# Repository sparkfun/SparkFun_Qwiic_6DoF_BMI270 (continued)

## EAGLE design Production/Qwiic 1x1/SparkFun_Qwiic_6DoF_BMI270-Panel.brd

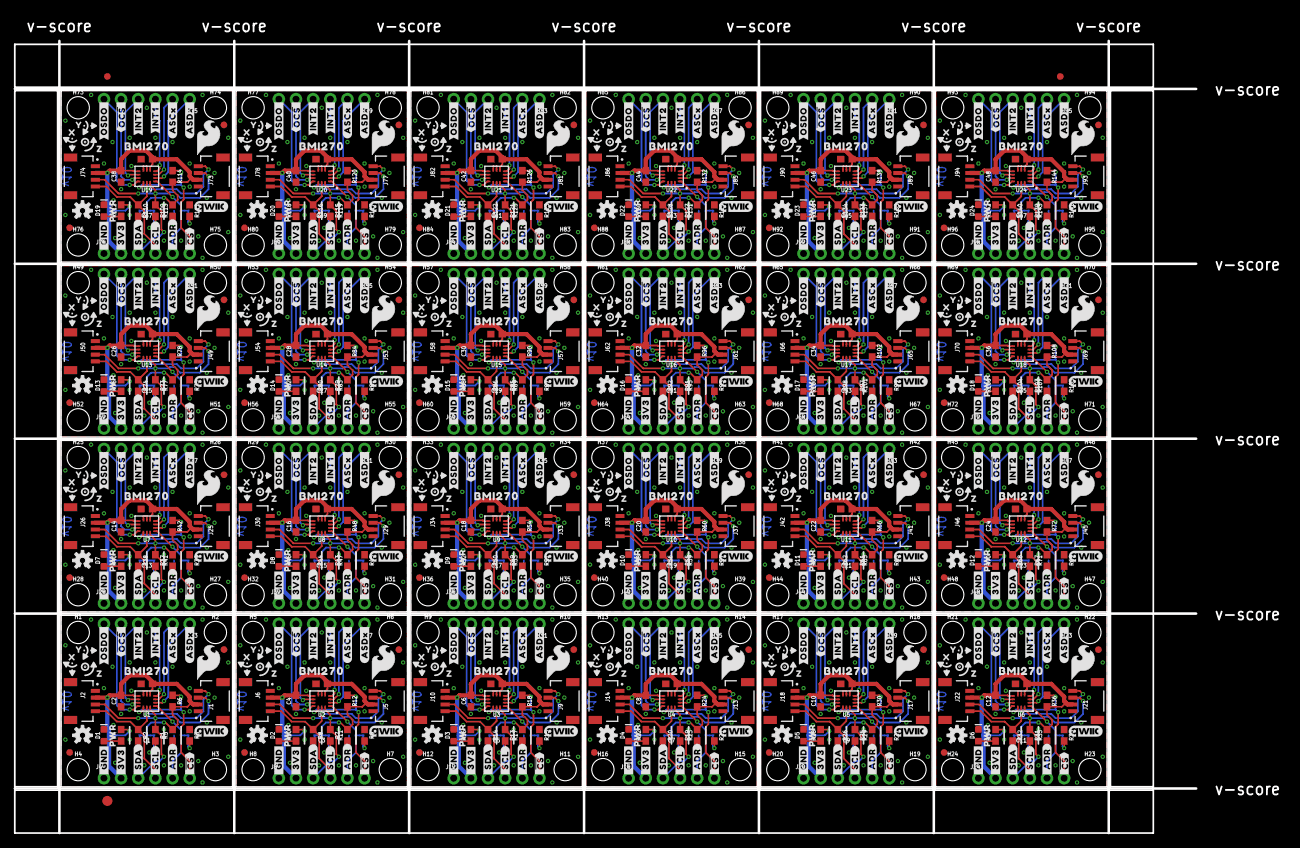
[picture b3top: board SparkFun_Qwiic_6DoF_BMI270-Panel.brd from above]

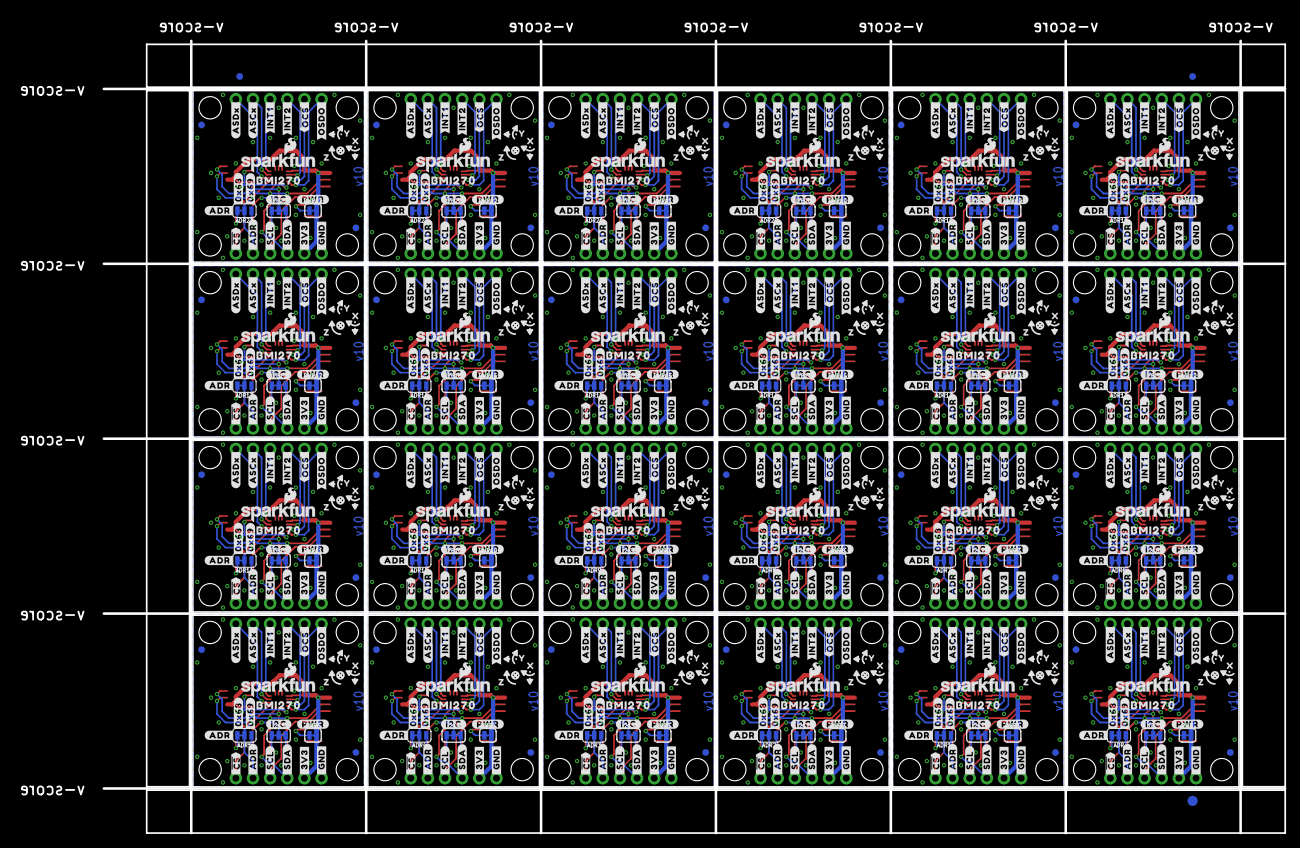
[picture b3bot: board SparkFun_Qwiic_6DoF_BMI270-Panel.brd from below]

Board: 2 copper layers, 175.0 x 117.3 mm, 1614 parts (651 on the bottom side), 432 nets.

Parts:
ADR, ADR1, ADR2, ADR3, ADR4, ADR5, ADR6, ADR7, ADR8, ADR9, ADR10, ADR11, ADR12, ADR13, ADR14, ADR15, ADR16, ADR17, ADR18, ADR19, ADR20, ADR21, ADR22, ADR23: JUMPER-SMT_3_1-NC_TRACE_SILK; SMT-JUMPER_3_1-NC_TRACE_SILK
C1, C2, C3, C4, C5, C6, C7, C8, C9, C10, C11, C12, C13, C14, C15, C16, C17, C18, C19, C20, C21, C22, C23, C24, C25, C26, C27, C28, C29, C30, C31, C32, C33, C34, C35, C36, C37, C38, C39, C40, C41, C42, C43, C44, C45, C46, C47, C48: 0.1uF; 0603
D1, D2, D3, D4, D5, D6, D7, D8, D9, D10, D11, D12, D13, D14, D15, D16, D17, D18, D19, D20, D21, D22, D23, D24: RED; LED-0603
E$1, E$2, E$3, E$4: FIDUCIAL-1X2
E$5, E$6: FIDUCIAL-1.5X3
FD1, FD2, FD3, FD4, FD5, FD6, FD7, FD8, FD9, FD10, FD11, FD12, FD13, FD14, FD15, FD16, FD17, FD18, FD19, FD20, FD21, FD22, FD23, FD24, FD25, FD26, FD27, FD28, FD29, FD30, FD31, FD32, FD33, FD34, FD35, FD36, FD37, FD38, FD39, FD40, FD41, FD42, FD43, FD44, FD45, FD46, FD47, FD48, FD49, FD50, FD51, FD52, FD53, FD54, FD55, FD56, FD57, FD58, FD59, FD60, FD61, FD62, FD63, FD64, FD65, FD66, FD67, FD68, FD69, FD70, FD71, FD72, FD73, FD74, FD75, FD76, FD77, FD78, FD79, FD80, FD81, FD82, FD83, FD84, FD85, FD86, FD87, FD88, FD89, FD90, FD91, FD92, FD93, FD94, FD95, FD96: FIDUCIAL1X2; FIDUCIAL-1X2
H1, H2, H3, H4, H5, H6, H7, H8, H9, H10, H11, H12, H13, H14, H15, H16, H17, H18, H19, H20, H21, H22, H23, H24, H25, H26, H27, H28, H29, H30, H31, H32, H33, H34, H35, H36, H37, H38, H39, H40, H41, H42, H43, H44, H45, H46, H47, H48, H49, H50, H51, H52, H53, H54, H55, H56, H57, H58, H59, H60, H61, H62, H63, H64, H65, H66, H67, H68, H69, H70, H71, H72, H73, H74, H75, H76, H77, H78, H79, H80, H81, H82, H83, H84, H85, H86, H87, H88, H89, H90, H91, H92, H93, H94, H95, H96: STAND-OFF
I2C, I2C1, I2C2, I2C3, I2C4, I2C5, I2C6, I2C7, I2C8, I2C9, I2C10, I2C11, I2C12, I2C13, I2C14, I2C15, I2C16, I2C17, I2C18, I2C19, I2C20, I2C21, I2C22, I2C23: JUMPER-SMT_3_2-NC_TRACE_SILK; SMT-JUMPER_3_2-NC_TRACE_SILK
J1, J2, J5, J6, J9, J10, J13, J14, J17, J18, J21, J22, J25, J26, J29, J30, J33, J34, J37, J38, J41, J42, J45, J46, J49, J50, J53, J54, J57, J58, J61, J62, J65, J66, J69, J70, J73, J74, J77, J78, J81, J82, J85, J86, J89, J90, J93, J94: QWIIC_RIGHT_ANGLE; JST04_1MM_RA
J3, J4, J7, J8, J11, J12, J15, J16, J19, J20, J23, J24, J27, J28, J31, J32, J35, J36, J39, J40, J43, J44, J47, J48, J51, J52, J55, J56, J59, J60, J63, J64, J67, J68, J71, J72, J75, J76, J79, J80, J83, J84, J87, J88, J91, J92, J95, J96: 1X06_NO_SILK
LOGO1, LOGO4, LOGO7, LOGO10, LOGO13, LOGO16, LOGO19, LOGO22, LOGO25, LOGO28, LOGO31, LOGO34, LOGO37, LOGO40, LOGO43, LOGO46, LOGO49, LOGO52, LOGO55, LOGO58, LOGO61, LOGO64, LOGO67, LOGO70: SFE_LOGO_NAME_FLAME.1_INCH; SFE_LOGO_NAME_FLAME_.1
LOGO2, LOGO5, LOGO8, LOGO11, LOGO14, LOGO17, LOGO20, LOGO23, LOGO26, LOGO29, LOGO32, LOGO35, LOGO38, LOGO41, LOGO44, LOGO47, LOGO50, LOGO53, LOGO56, LOGO59, LOGO62, LOGO65, LOGO68, LOGO71: QWIIC_LOGO_5MM; QWIIC_5MM
LOGO3, LOGO6, LOGO9, LOGO12, LOGO15, LOGO18, LOGO21, LOGO24, LOGO27, LOGO30, LOGO33, LOGO36, LOGO39, LOGO42, LOGO45, LOGO48, LOGO51, LOGO54, LOGO57, LOGO60, LOGO63, LOGO66, LOGO69, LOGO72: OSHW-LOGOS; OSHW-LOGO-S
PWR, PWR1, PWR2, PWR3, PWR4, PWR5, PWR6, PWR7, PWR8, PWR9, PWR10, PWR11, PWR12, PWR13, PWR14, PWR15, PWR16, PWR17, PWR18, PWR19, PWR20, PWR21, PWR22, PWR23: JUMPER-SMT_2_NC_TRACE_SILK; SMT-JUMPER_2_NC_TRACE_SILK
R1, R2, R7, R8, R13, R14, R19, R20, R25, R26, R31, R32, R37, R38, R43, R44, R49, R50, R55, R56, R61, R62, R67, R68, R73, R74, R79, R80, R85, R86, R91, R92, R97, R98, R103, R104, R109, R110, R115, R116, R121, R122, R127, R128, R133, R134, R139, R140: 2.2k; 0603
R3, R5, R6, R9, R11, R12, R15, R17, R18, R21, R23, R24, R27, R29, R30, R33, R35, R36, R39, R41, R42, R45, R47, R48, R51, R53, R54, R57, R59, R60, R63, R65, R66, R69, R71, R72, R75, R77, R78, R81, R83, R84, R87, R89, R90, R93, R95, R96, R99, R101, R102, R105, R107, R108, R111, R113, R114, R117, R119, R120, R123, R125, R126, R129, R131, R132, R135, R137, R138, R141, R143, R144: 100k; 0603
R4, R10, R16, R22, R28, R34, R40, R46, R52, R58, R64, R70, R76, R82, R88, R94, R100, R106, R112, R118, R124, R130, R136, R142: 4.7k; 0603
U1, U2, U3, U4, U5, U6, U7, U8, U9, U10, U11, U12, U13, U14, U15, U16, U17, U18, U19, U20, U21, U22, U23, U24: BMI270
U$1, U$38, U$77, U$122, U$161, U$200, U$239, U$278, U$317, U$356, U$395, U$434, U$473, U$512, U$551, U$590, U$629, U$668, U$707, U$746, U$785, U$824, U$863, U$902: #I2C#0
U$2, U$14, U$47, U$59, U$92, U$104, U$131, U$143, U$170, U$182, U$209, U$221, U$248, U$260, U$287, U$299, U$326, U$338, U$365, U$377, U$404, U$416, U$443, U$455, U$482, U$494, U$521, U$533, U$560, U$572, U$599, U$611, U$638, U$650, U$677, U$689, U$716, U$728, U$755, U$767, U$794, U$806, U$833, U$845, U$872, U$884, U$911, U$923: #_SDA#0
U$3, U$37, U$76, U$121, U$160, U$199, U$238, U$277, U$316, U$355, U$394, U$433, U$472, U$511, U$550, U$589, U$628, U$667, U$706, U$745, U$784, U$823, U$862, U$901: SFE_LOGO_FLAME_.2
U$4, U$39, U$78, U$123, U$162, U$201, U$240, U$279, U$318, U$357, U$396, U$435, U$474, U$513, U$552, U$591, U$630, U$669, U$708, U$747, U$786, U$825, U$864, U$903: #PWR#0
U$5, U$40, U$82, U$124, U$163, U$202, U$241, U$280, U$319, U$358, U$397, U$436, U$475, U$514, U$553, U$592, U$631, U$670, U$709, U$748, U$787, U$826, U$865, U$904: #ADR#0
U$6, U$41, U$83, U$125, U$164, U$203, U$242, U$281, U$320, U$359, U$398, U$437, U$476, U$515, U$554, U$593, U$632, U$671, U$710, U$749, U$788, U$827, U$866, U$905: #0X68#0
U$7, U$13, U$46, U$58, U$91, U$103, U$130, U$142, U$169, U$181, U$208, U$220, U$247, U$259, U$286, U$298, U$325, U$337, U$364, U$376, U$403, U$415, U$442, U$454, U$481, U$493, U$520, U$532, U$559, U$571, U$598, U$610, U$637, U$649, U$676, U$688, U$715, U$727, U$754, U$766, U$793, U$805, U$832, U$844, U$871, U$883, U$910, U$922: #_3V3#0
U$8, U$17, U$50, U$62, U$95, U$107, U$134, U$146, U$173, U$185, U$212, U$224, U$251, U$263, U$290, U$302, U$329, U$341, U$368, U$380, U$407, U$419, U$446, U$458, U$485, U$497, U$524, U$536, U$563, U$575, U$602, U$614, U$641, U$653, U$680, U$692, U$719, U$731, U$758, U$770, U$797, U$809, U$836, U$848, U$875, U$887, U$914, U$926: #_#CS##0
U$9, U$16, U$49, U$61, U$94, U$106, U$133, U$145, U$172, U$184, U$211, U$223, U$250, U$262, U$289, U$301, U$328, U$340, U$367, U$379, U$406, U$418, U$445, U$457, U$484, U$496, U$523, U$535, U$562, U$574, U$601, U$613, U$640, U$652, U$679, U$691, U$718, U$730, U$757, U$769, U$796, U$808, U$835, U$847, U$874, U$886, U$913, U$925: #_ADR#0
U$10, U$15, U$48, U$60, U$93, U$105, U$132, U$144, U$171, U$183, U$210, U$222, U$249, U$261, U$288, U$300, U$327, U$339, U$366, U$378, U$405, U$417, U$444, U$456, U$483, U$495, U$522, U$534, U$561, U$573, U$600, U$612, U$639, U$651, U$678, U$690, U$717, U$729, U$756, U$768, U$795, U$807, U$834, U$846, U$873, U$885, U$912, U$924: #_SCL#0
U$11, U$27, U$51, U$63, U$96, U$108, U$135, U$147, U$174, U$186, U$213, U$225, U$252, U$264, U$291, U$303, U$330, U$342, U$369, U$381, U$408, U$420, U$447, U$459, U$486, U$498, U$525, U$537, U$564, U$576, U$603, U$615, U$642, U$654, U$681, U$693, U$720, U$732, U$759, U$771, U$798, U$810, U$837, U$849, U$876, U$888, U$915, U$927: #ASDX_#0
U$12, U$19, U$45, U$57, U$87, U$102, U$129, U$141, U$168, U$180, U$207, U$219, U$246, U$258, U$285, U$297, U$324, U$336, U$363, U$375, U$402, U$414, U$441, U$453, U$480, U$492, U$519, U$531, U$558, U$570, U$597, U$609, U$636, U$648, U$675, U$687, U$714, U$726, U$753, U$765, U$792, U$804, U$831, U$843, U$870, U$882, U$909, U$921: #_GND#0
U$18, U$42, U$84, U$126, U$165, U$204, U$243, U$282, U$321, U$360, U$399, U$438, U$477, U$516, U$555, U$594, U$633, U$672, U$711, U$750, U$789, U$828, U$867, U$906: #0X69#0
U$20, U$21, U$43, U$44, U$85, U$86, U$127, U$128, U$166, U$167, U$205, U$206, U$244, U$245, U$283, U$284, U$322, U$323, U$361, U$362, U$400, U$401, U$439, U$440, U$478, U$479, U$517, U$518, U$556, U$557, U$595, U$596, U$634, U$635, U$673, U$674, U$712, U$713, U$751, U$752, U$790, U$791, U$829, U$830, U$868, U$869, U$907, U$908: BMI2700
U$22, U$28, U$52, U$64, U$97, U$109, U$136, U$148, U$175, U$187, U$214, U$226, U$253, U$265, U$292, U$304, U$331, U$343, U$370, U$382, U$409, U$421, U$448, U$460, U$487, U$499, U$526, U$538, U$565, U$577, U$604, U$616, U$643, U$655, U$682, U$694, U$721, U$733, U$760, U$772, U$799, U$811, U$838, U$850, U$877, U$889, U$916, U$928: #ASCX_#0
U$23, U$29, U$53, U$65, U$98, U$110, U$137, U$149, U$176, U$188, U$215, U$227, U$254, U$266, U$293, U$305, U$332, U$344, U$371, U$383, U$410, U$422, U$449, U$461, U$488, U$500, U$527, U$539, U$566, U$578, U$605, U$617, U$644, U$656, U$683, U$695, U$722, U$734, U$761, U$773, U$800, U$812, U$839, U$851, U$878, U$890, U$917, U$929: #INT1_#0
U$24, U$30, U$54, U$66, U$99, U$111, U$138, U$150, U$177, U$189, U$216, U$228, U$255, U$267, U$294, U$306, U$333, U$345, U$372, U$384, U$411, U$423, U$450, U$462, U$489, U$501, U$528, U$540, U$567, U$579, U$606, U$618, U$645, U$657, U$684, U$696, U$723, U$735, U$762, U$774, U$801, U$813, U$840, U$852, U$879, U$891, U$918, U$930: #INT2_#0
U$25, U$31, U$55, U$67, U$100, U$112, U$139, U$151, U$178, U$190, U$217, U$229, U$256, U$268, U$295, U$307, U$334, U$346, U$373, U$385, U$412, U$424, U$451, U$463, U$490, U$502, U$529, U$541, U$568, U$580, U$607, U$619, U$646, U$658, U$685, U$697, U$724, U$736, U$763, U$775, U$802, U$814, U$841, U$853, U$880, U$892, U$919, U$931: ##OCS#_#0
U$26, U$32, U$56, U$68, U$101, U$113, U$140, U$152, U$179, U$191, U$218, U$230, U$257, U$269, U$296, U$308, U$335, U$347, U$374, U$386, U$413, U$425, U$452, U$464, U$491, U$503, U$530, U$542, U$569, U$581, U$608, U$620, U$647, U$659, U$686, U$698, U$725, U$737, U$764, U$776, U$803, U$815, U$842, U$854, U$881, U$893, U$920, U$932: #OSDO_#0
U$33, U$69, U$73, U$79, U$88, U$114, U$118, U$153, U$157, U$192, U$196, U$231, U$235, U$270, U$274, U$309, U$313, U$348, U$352, U$387, U$391, U$426, U$430, U$465, U$469, U$504, U$508, U$543, U$547, U$582, U$586, U$621, U$625, U$660, U$664, U$699, U$703, U$738, U$742, U$777, U$781, U$816, U$820, U$855, U$859, U$894, U$898, U$933: X0
U$34, U$72, U$117, U$156, U$195, U$234, U$273, U$312, U$351, U$390, U$429, U$468, U$507, U$546, U$585, U$624, U$663, U$702, U$741, U$780, U$819, U$858, U$897, U$936: PWR0
U$35, U$70, U$74, U$80, U$89, U$115, U$119, U$154, U$158, U$193, U$197, U$232, U$236, U$271, U$275, U$310, U$314, U$349, U$353, U$388, U$392, U$427, U$431, U$466, U$470, U$505, U$509, U$544, U$548, U$583, U$587, U$622, U$626, U$661, U$665, U$700, U$704, U$739, U$743, U$778, U$782, U$817, U$821, U$856, U$860, U$895, U$899, U$934: Y0
U$36, U$71, U$75, U$81, U$90, U$116, U$120, U$155, U$159, U$194, U$198, U$233, U$237, U$272, U$276, U$311, U$315, U$350, U$354, U$389, U$393, U$428, U$432, U$467, U$471, U$506, U$510, U$545, U$549, U$584, U$588, U$623, U$627, U$662, U$666, U$701, U$705, U$740, U$744, U$779, U$783, U$818, U$822, U$857, U$861, U$896, U$900, U$935: Z0

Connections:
3.3V: C1.2, C2.2, I2C.2, J1.2, J2.2, J4.2, PWR.2, R5.2, R6.2, U1.5, U1.8
3.3V1: C3.2, C4.2, I2C1.2, J5.2, J6.2, J8.2, PWR1.2, R11.2, R12.2, U2.5, U2.8
3.3V2: C5.2, C6.2, I2C2.2, J9.2, J10.2, J12.2, PWR2.2, R17.2, R18.2, U3.5, U3.8
3.3V3: C7.2, C8.2, I2C3.2, J13.2, J14.2, J16.2, PWR3.2, R23.2, R24.2, U4.5, U4.8
3.3V4: C9.2, C10.2, I2C4.2, J17.2, J18.2, J20.2, PWR4.2, R29.2, R30.2, U5.5, U5.8
3.3V5: C11.2, C12.2, I2C5.2, J21.2, J22.2, J24.2, PWR5.2, R35.2, R36.2, U6.5, U6.8
3.3V6: C13.2, C14.2, I2C6.2, J25.2, J26.2, J28.2, PWR6.2, R41.2, R42.2, U7.5, U7.8
3.3V7: C15.2, C16.2, I2C7.2, J29.2, J30.2, J32.2, PWR7.2, R47.2, R48.2, U8.5, U8.8
3.3V8: C17.2, C18.2, I2C8.2, J33.2, J34.2, J36.2, PWR8.2, R53.2, R54.2, U9.5, U9.8
3.3V9: C19.2, C20.2, I2C9.2, J37.2, J38.2, J40.2, PWR9.2, R59.2, R60.2, U10.5, U10.8
3.3V10: C21.2, C22.2, I2C10.2, J41.2, J42.2, J44.2, PWR10.2, R65.2, R66.2, U11.5, U11.8
3.3V11: C23.2, C24.2, I2C11.2, J45.2, J46.2, J48.2, PWR11.2, R71.2, R72.2, U12.5, U12.8
3.3V12: C25.2, C26.2, I2C12.2, J49.2, J50.2, J52.2, PWR12.2, R77.2, R78.2, U13.5, U13.8
3.3V13: C27.2, C28.2, I2C13.2, J53.2, J54.2, J56.2, PWR13.2, R83.2, R84.2, U14.5, U14.8
3.3V14: C29.2, C30.2, I2C14.2, J57.2, J58.2, J60.2, PWR14.2, R89.2, R90.2, U15.5, U15.8
3.3V15: C31.2, C32.2, I2C15.2, J61.2, J62.2, J64.2, PWR15.2, R95.2, R96.2, U16.5, U16.8
3.3V16: C33.2, C34.2, I2C16.2, J65.2, J66.2, J68.2, PWR16.2, R101.2, R102.2, U17.5, U17.8
3.3V17: C35.2, C36.2, I2C17.2, J69.2, J70.2, J72.2, PWR17.2, R107.2, R108.2, U18.5, U18.8
3.3V18: C37.2, C38.2, I2C18.2, J73.2, J74.2, J76.2, PWR18.2, R113.2, R114.2, U19.5, U19.8
3.3V19: C39.2, C40.2, I2C19.2, J77.2, J78.2, J80.2, PWR19.2, R119.2, R120.2, U20.5, U20.8
3.3V20: C41.2, C42.2, I2C20.2, J81.2, J82.2, J84.2, PWR20.2, R125.2, R126.2, U21.5, U21.8
3.3V21: C43.2, C44.2, I2C21.2, J85.2, J86.2, J88.2, PWR21.2, R131.2, R132.2, U22.5, U22.8
3.3V22: C45.2, C46.2, I2C22.2, J89.2, J90.2, J92.2, PWR22.2, R137.2, R138.2, U23.5, U23.8
3.3V23: C47.2, C48.2, I2C23.2, J93.2, J94.2, J96.2, PWR23.2, R143.2, R144.2, U24.5, U24.8
!CS!: J4.6, R6.1, U1.12
!CS!1: J8.6, R12.1, U2.12
!CS!2: J12.6, R18.1, U3.12
!CS!3: J16.6, R24.1, U4.12
!CS!4: J20.6, R30.1, U5.12
!CS!5: J24.6, R36.1, U6.12
!CS!6: J28.6, R42.1, U7.12
!CS!7: J32.6, R48.1, U8.12
!CS!8: J36.6, R54.1, U9.12
!CS!9: J40.6, R60.1, U10.12
!CS!10: J44.6, R66.1, U11.12
!CS!11: J48.6, R72.1, U12.12
!CS!12: J52.6, R78.1, U13.12
!CS!13: J56.6, R84.1, U14.12
!CS!14: J60.6, R90.1, U15.12
!CS!15: J64.6, R96.1, U16.12
!CS!16: J68.6, R102.1, U17.12
!CS!17: J72.6, R108.1, U18.12
!CS!18: J76.6, R114.1, U19.12
!CS!19: J80.6, R120.1, U20.12
!CS!20: J84.6, R126.1, U21.12
!CS!21: J88.6, R132.1, U22.12
!CS!22: J92.6, R138.1, U23.12
!CS!23: J96.6, R144.1, U24.12
!OCS!: J3.5, U1.10
!OCS!1: J7.5, U2.10
!OCS!2: J11.5, U3.10
!OCS!3: J15.5, U4.10
!OCS!4: J19.5, U5.10
!OCS!5: J23.5, U6.10
!OCS!6: J27.5, U7.10
!OCS!7: J31.5, U8.10
!OCS!8: J35.5, U9.10
!OCS!9: J39.5, U10.10
!OCS!10: J43.5, U11.10
!OCS!11: J47.5, U12.10
!OCS!12: J51.5, U13.10
!OCS!13: J55.5, U14.10
!OCS!14: J59.5, U15.10
!OCS!15: J63.5, U16.10
!OCS!16: J67.5, U17.10
!OCS!17: J71.5, U18.10
!OCS!18: J75.5, U19.10
!OCS!19: J79.5, U20.10
!OCS!20: J83.5, U21.10
!OCS!21: J87.5, U22.10
!OCS!22: J91.5, U23.10
!OCS!23: J95.5, U24.10
ADR/POCI: ADR.2, J4.5, U1.1
ADR/POCI1: ADR1.2, J8.5, U2.1
ADR/POCI2: ADR2.2, J12.5, U3.1
ADR/POCI3: ADR3.2, J16.5, U4.1
ADR/POCI4: ADR4.2, J20.5, U5.1
ADR/POCI5: ADR5.2, J24.5, U6.1
ADR/POCI6: ADR6.2, J28.5, U7.1
ADR/POCI7: ADR7.2, J32.5, U8.1
ADR/POCI8: ADR8.2, J36.5, U9.1
ADR/POCI9: ADR9.2, J40.5, U10.1
ADR/POCI10: ADR10.2, J44.5, U11.1
ADR/POCI11: ADR11.2, J48.5, U12.1
ADR/POCI12: ADR12.2, J52.5, U13.1
ADR/POCI13: ADR13.2, J56.5, U14.1
ADR/POCI14: ADR14.2, J60.5, U15.1
ADR/POCI15: ADR15.2, J64.5, U16.1
ADR/POCI16: ADR16.2, J68.5, U17.1
ADR/POCI17: ADR17.2, J72.5, U18.1
ADR/POCI18: ADR18.2, J76.5, U19.1
ADR/POCI19: ADR19.2, J80.5, U20.1
ADR/POCI20: ADR20.2, J84.5, U21.1
ADR/POCI21: ADR21.2, J88.5, U22.1
ADR/POCI22: ADR22.2, J92.5, U23.1
ADR/POCI23: ADR23.2, J96.5, U24.1
ASCX: J3.2, U1.3
ASCX1: J7.2, U2.3
ASCX2: J11.2, U3.3
ASCX3: J15.2, U4.3
ASCX4: J19.2, U5.3
ASCX5: J23.2, U6.3
ASCX6: J27.2, U7.3
ASCX7: J31.2, U8.3
ASCX8: J35.2, U9.3
ASCX9: J39.2, U10.3
ASCX10: J43.2, U11.3
ASCX11: J47.2, U12.3
ASCX12: J51.2, U13.3
ASCX13: J55.2, U14.3
ASCX14: J59.2, U15.3
ASCX15: J63.2, U16.3
ASCX16: J67.2, U17.3
ASCX17: J71.2, U18.3
ASCX18: J75.2, U19.3
ASCX19: J79.2, U20.3
ASCX20: J83.2, U21.3
ASCX21: J87.2, U22.3
ASCX22: J91.2, U23.3
ASCX23: J95.2, U24.3
ASDX: J3.1, U1.2
ASDX1: J7.1, U2.2
ASDX2: J11.1, U3.2
ASDX3: J15.1, U4.2
ASDX4: J19.1, U5.2
ASDX5: J23.1, U6.2
ASDX6: J27.1, U7.2
ASDX7: J31.1, U8.2
ASDX8: J35.1, U9.2
ASDX9: J39.1, U10.2
ASDX10: J43.1, U11.2
ASDX11: J47.1, U12.2
ASDX12: J51.1, U13.2
ASDX13: J55.1, U14.2
ASDX14: J59.1, U15.2
ASDX15: J63.1, U16.2
ASDX16: J67.1, U17.2
ASDX17: J71.1, U18.2
ASDX18: J75.1, U19.2
ASDX19: J79.1, U20.2
ASDX20: J83.1, U21.2
ASDX21: J87.1, U22.2
ASDX22: J91.1, U23.2
ASDX23: J95.1, U24.2
GND: C1.1, C2.1, D1.C, J1.1, J2.1, J4.1, R3.1, U1.6, U1.7
GND1: C3.1, C4.1, D2.C, J5.1, J6.1, J8.1, R9.1, U2.6, U2.7
GND2: C5.1, C6.1, D3.C, J9.1, J10.1, J12.1, R15.1, U3.6, U3.7
GND3: C7.1, C8.1, D4.C, J13.1, J14.1, J16.1, R21.1, U4.6, U4.7
GND4: C9.1, C10.1, D5.C, J17.1, J18.1, J20.1, R27.1, U5.6, U5.7
GND5: C11.1, C12.1, D6.C, J21.1, J22.1, J24.1, R33.1, U6.6, U6.7
GND6: C13.1, C14.1, D7.C, J25.1, J26.1, J28.1, R39.1, U7.6, U7.7
GND7: C15.1, C16.1, D8.C, J29.1, J30.1, J32.1, R45.1, U8.6, U8.7
GND8: C17.1, C18.1, D9.C, J33.1, J34.1, J36.1, R51.1, U9.6, U9.7
GND9: C19.1, C20.1, D10.C, J37.1, J38.1, J40.1, R57.1, U10.6, U10.7
GND10: C21.1, C22.1, D11.C, J41.1, J42.1, J44.1, R63.1, U11.6, U11.7
GND11: C23.1, C24.1, D12.C, J45.1, J46.1, J48.1, R69.1, U12.6, U12.7
GND12: C25.1, C26.1, D13.C, J49.1, J50.1, J52.1, R75.1, U13.6, U13.7
GND13: C27.1, C28.1, D14.C, J53.1, J54.1, J56.1, R81.1, U14.6, U14.7
GND14: C29.1, C30.1, D15.C, J57.1, J58.1, J60.1, R87.1, U15.6, U15.7
GND15: C31.1, C32.1, D16.C, J61.1, J62.1, J64.1, R93.1, U16.6, U16.7
GND16: C33.1, C34.1, D17.C, J65.1, J66.1, J68.1, R99.1, U17.6, U17.7
GND17: C35.1, C36.1, D18.C, J69.1, J70.1, J72.1, R105.1, U18.6, U18.7
GND18: C37.1, C38.1, D19.C, J73.1, J74.1, J76.1, R111.1, U19.6, U19.7
GND19: C39.1, C40.1, D20.C, J77.1, J78.1, J80.1, R117.1, U20.6, U20.7
GND20: C41.1, C42.1, D21.C, J81.1, J82.1, J84.1, R123.1, U21.6, U21.7
GND21: C43.1, C44.1, D22.C, J85.1, J86.1, J88.1, R129.1, U22.6, U22.7
GND22: C45.1, C46.1, D23.C, J89.1, J90.1, J92.1, R135.1, U23.6, U23.7
GND23: C47.1, C48.1, D24.C, J93.1, J94.1, J96.1, R141.1, U24.6, U24.7
INT1: J3.3, U1.4
INT2: J3.4, U1.9
INT3: J7.3, U2.4
INT4: J7.4, U2.9
INT5: J11.3, U3.4
INT6: J11.4, U3.9
INT7: J15.3, U4.4
INT8: J15.4, U4.9
INT9: J19.3, U5.4
INT10: J19.4, U5.9
INT11: J23.3, U6.4
INT12: J23.4, U6.9
INT13: J27.3, U7.4
INT14: J27.4, U7.9
INT15: J31.3, U8.4
INT16: J31.4, U8.9
INT17: J35.3, U9.4
INT18: J35.4, U9.9
INT19: J39.3, U10.4
INT20: J39.4, U10.9
INT21: J43.3, U11.4
INT22: J43.4, U11.9
INT23: J47.3, U12.4
INT24: J47.4, U12.9
INT25: J51.3, U13.4
INT26: J51.4, U13.9
INT27: J55.3, U14.4
INT28: J55.4, U14.9
INT29: J59.3, U15.4
INT30: J59.4, U15.9
INT31: J63.3, U16.4
INT32: J63.4, U16.9
INT33: J67.3, U17.4
INT34: J67.4, U17.9
INT35: J71.3, U18.4
INT36: J71.4, U18.9
INT37: J75.3, U19.4
INT38: J75.4, U19.9
INT39: J79.3, U20.4
INT40: J79.4, U20.9
INT41: J83.3, U21.4
INT42: J83.4, U21.9
INT43: J87.3, U22.4
INT44: J87.4, U22.9
INT45: J91.3, U23.4
INT46: J91.4, U23.9
INT47: J95.3, U24.4
INT48: J95.4, U24.9
unnamed: I2C.1, R1.2
unnamed: I2C.3, R2.2
unnamed: PWR.1, R4.2
unnamed: D1.A, R4.1
unnamed: ADR.1, R5.1
unnamed: ADR.3, R3.2
unnamed: I2C1.1, R7.2
unnamed: I2C1.3, R8.2
unnamed: PWR1.1, R10.2
unnamed: D2.A, R10.1
unnamed: ADR1.1, R11.1
unnamed: ADR1.3, R9.2
unnamed: I2C2.1, R13.2
unnamed: I2C2.3, R14.2
unnamed: PWR2.1, R16.2
unnamed: D3.A, R16.1
unnamed: ADR2.1, R17.1
unnamed: ADR2.3, R15.2
unnamed: I2C3.1, R19.2
unnamed: I2C3.3, R20.2
unnamed: PWR3.1, R22.2
unnamed: D4.A, R22.1
unnamed: ADR3.1, R23.1
unnamed: ADR3.3, R21.2
unnamed: I2C4.1, R25.2
unnamed: I2C4.3, R26.2
unnamed: PWR4.1, R28.2
unnamed: D5.A, R28.1
unnamed: ADR4.1, R29.1
unnamed: ADR4.3, R27.2
unnamed: I2C5.1, R31.2
unnamed: I2C5.3, R32.2
unnamed: PWR5.1, R34.2
unnamed: D6.A, R34.1
unnamed: ADR5.1, R35.1
unnamed: ADR5.3, R33.2
unnamed: I2C6.1, R37.2
unnamed: I2C6.3, R38.2
unnamed: PWR6.1, R40.2
unnamed: D7.A, R40.1
unnamed: ADR6.1, R41.1
unnamed: ADR6.3, R39.2
unnamed: I2C7.1, R43.2
unnamed: I2C7.3, R44.2
unnamed: PWR7.1, R46.2
unnamed: D8.A, R46.1
unnamed: ADR7.1, R47.1
unnamed: ADR7.3, R45.2
unnamed: I2C8.1, R49.2
unnamed: I2C8.3, R50.2
unnamed: PWR8.1, R52.2
unnamed: D9.A, R52.1
unnamed: ADR8.1, R53.1
unnamed: ADR8.3, R51.2
unnamed: I2C9.1, R55.2
unnamed: I2C9.3, R56.2
unnamed: PWR9.1, R58.2
unnamed: D10.A, R58.1
unnamed: ADR9.1, R59.1
unnamed: ADR9.3, R57.2
unnamed: I2C10.1, R61.2
unnamed: I2C10.3, R62.2
unnamed: PWR10.1, R64.2
unnamed: D11.A, R64.1
unnamed: ADR10.1, R65.1
unnamed: ADR10.3, R63.2
unnamed: I2C11.1, R67.2
unnamed: I2C11.3, R68.2
unnamed: PWR11.1, R70.2
unnamed: D12.A, R70.1
unnamed: ADR11.1, R71.1
unnamed: ADR11.3, R69.2
unnamed: I2C12.1, R73.2
unnamed: I2C12.3, R74.2
unnamed: PWR12.1, R76.2
unnamed: D13.A, R76.1
unnamed: ADR12.1, R77.1
unnamed: ADR12.3, R75.2
unnamed: I2C13.1, R79.2
unnamed: I2C13.3, R80.2
unnamed: PWR13.1, R82.2
unnamed: D14.A, R82.1
unnamed: ADR13.1, R83.1
unnamed: ADR13.3, R81.2
unnamed: I2C14.1, R85.2
unnamed: I2C14.3, R86.2
unnamed: PWR14.1, R88.2
unnamed: D15.A, R88.1
unnamed: ADR14.1, R89.1
unnamed: ADR14.3, R87.2
unnamed: I2C15.1, R91.2
unnamed: I2C15.3, R92.2
unnamed: PWR15.1, R94.2
unnamed: D16.A, R94.1
unnamed: ADR15.1, R95.1
unnamed: ADR15.3, R93.2
unnamed: I2C16.1, R97.2
unnamed: I2C16.3, R98.2
unnamed: PWR16.1, R100.2
unnamed: D17.A, R100.1
unnamed: ADR16.1, R101.1
unnamed: ADR16.3, R99.2
unnamed: I2C17.1, R103.2
unnamed: I2C17.3, R104.2
unnamed: PWR17.1, R106.2
unnamed: D18.A, R106.1
unnamed: ADR17.1, R107.1
unnamed: ADR17.3, R105.2
unnamed: I2C18.1, R109.2
unnamed: I2C18.3, R110.2
unnamed: PWR18.1, R112.2
unnamed: D19.A, R112.1
unnamed: ADR18.1, R113.1
unnamed: ADR18.3, R111.2
unnamed: I2C19.1, R115.2
unnamed: I2C19.3, R116.2
unnamed: PWR19.1, R118.2
unnamed: D20.A, R118.1
unnamed: ADR19.1, R119.1
unnamed: ADR19.3, R117.2
unnamed: I2C20.1, R121.2
unnamed: I2C20.3, R122.2
unnamed: PWR20.1, R124.2
unnamed: D21.A, R124.1
unnamed: ADR20.1, R125.1
unnamed: ADR20.3, R123.2
unnamed: I2C21.1, R127.2
unnamed: I2C21.3, R128.2
unnamed: PWR21.1, R130.2
unnamed: D22.A, R130.1
unnamed: ADR21.1, R131.1
unnamed: ADR21.3, R129.2
unnamed: I2C22.1, R133.2
unnamed: I2C22.3, R134.2
unnamed: PWR22.1, R136.2
unnamed: D23.A, R136.1
unnamed: ADR22.1, R137.1
unnamed: ADR22.3, R135.2
unnamed: I2C23.1, R139.2
unnamed: I2C23.3, R140.2
unnamed: PWR23.1, R142.2
unnamed: D24.A, R142.1
unnamed: ADR23.1, R143.1
unnamed: ADR23.3, R141.2
OSDO: J3.6, U1.11
OSDO1: J7.6, U2.11
OSDO2: J11.6, U3.11
OSDO3: J15.6, U4.11
OSDO4: J19.6, U5.11
OSDO5: J23.6, U6.11
OSDO6: J27.6, U7.11
OSDO7: J31.6, U8.11
OSDO8: J35.6, U9.11
OSDO9: J39.6, U10.11
OSDO10: J43.6, U11.11
OSDO11: J47.6, U12.11
OSDO12: J51.6, U13.11
OSDO13: J55.6, U14.11
OSDO14: J59.6, U15.11
OSDO15: J63.6, U16.11
OSDO16: J67.6, U17.11
OSDO17: J71.6, U18.11
OSDO18: J75.6, U19.11
OSDO19: J79.6, U20.11
OSDO20: J83.6, U21.11
OSDO21: J87.6, U22.11
OSDO22: J91.6, U23.11
OSDO23: J95.6, U24.11
SCL/SCK: J1.4, J2.4, J4.4, R2.1, U1.13
SCL/SCK1: J5.4, J6.4, J8.4, R8.1, U2.13
SCL/SCK2: J9.4, J10.4, J12.4, R14.1, U3.13
SCL/SCK3: J13.4, J14.4, J16.4, R20.1, U4.13
SCL/SCK4: J17.4, J18.4, J20.4, R26.1, U5.13
SCL/SCK5: J21.4, J22.4, J24.4, R32.1, U6.13
SCL/SCK6: J25.4, J26.4, J28.4, R38.1, U7.13
SCL/SCK7: J29.4, J30.4, J32.4, R44.1, U8.13
SCL/SCK8: J33.4, J34.4, J36.4, R50.1, U9.13
SCL/SCK9: J37.4, J38.4, J40.4, R56.1, U10.13
SCL/SCK10: J41.4, J42.4, J44.4, R62.1, U11.13
SCL/SCK11: J45.4, J46.4, J48.4, R68.1, U12.13
SCL/SCK12: J49.4, J50.4, J52.4, R74.1, U13.13
SCL/SCK13: J53.4, J54.4, J56.4, R80.1, U14.13
SCL/SCK14: J57.4, J58.4, J60.4, R86.1, U15.13
SCL/SCK15: J61.4, J62.4, J64.4, R92.1, U16.13
SCL/SCK16: J65.4, J66.4, J68.4, R98.1, U17.13
SCL/SCK17: J69.4, J70.4, J72.4, R104.1, U18.13
SCL/SCK18: J73.4, J74.4, J76.4, R110.1, U19.13
SCL/SCK19: J77.4, J78.4, J80.4, R116.1, U20.13
SCL/SCK20: J81.4, J82.4, J84.4, R122.1, U21.13
SCL/SCK21: J85.4, J86.4, J88.4, R128.1, U22.13
SCL/SCK22: J89.4, J90.4, J92.4, R134.1, U23.13
SCL/SCK23: J93.4, J94.4, J96.4, R140.1, U24.13
SDA/PICO: J1.3, J2.3, J4.3, R1.1, U1.14
SDA/PICO1: J5.3, J6.3, J8.3, R7.1, U2.14
SDA/PICO2: J9.3, J10.3, J12.3, R13.1, U3.14
SDA/PICO3: J13.3, J14.3, J16.3, R19.1, U4.14
SDA/PICO4: J17.3, J18.3, J20.3, R25.1, U5.14
SDA/PICO5: J21.3, J22.3, J24.3, R31.1, U6.14
SDA/PICO6: J25.3, J26.3, J28.3, R37.1, U7.14
SDA/PICO7: J29.3, J30.3, J32.3, R43.1, U8.14
SDA/PICO8: J33.3, J34.3, J36.3, R49.1, U9.14
SDA/PICO9: J37.3, J38.3, J40.3, R55.1, U10.14
SDA/PICO10: J41.3, J42.3, J44.3, R61.1, U11.14
SDA/PICO11: J45.3, J46.3, J48.3, R67.1, U12.14
SDA/PICO12: J49.3, J50.3, J52.3, R73.1, U13.14
SDA/PICO13: J53.3, J54.3, J56.3, R79.1, U14.14
SDA/PICO14: J57.3, J58.3, J60.3, R85.1, U15.14
SDA/PICO15: J61.3, J62.3, J64.3, R91.1, U16.14
SDA/PICO16: J65.3, J66.3, J68.3, R97.1, U17.14
SDA/PICO17: J69.3, J70.3, J72.3, R103.1, U18.14
SDA/PICO18: J73.3, J74.3, J76.3, R109.1, U19.14
SDA/PICO19: J77.3, J78.3, J80.3, R115.1, U20.14
SDA/PICO20: J81.3, J82.3, J84.3, R121.1, U21.14
SDA/PICO21: J85.3, J86.3, J88.3, R127.1, U22.14
SDA/PICO22: J89.3, J90.3, J92.3, R133.1, U23.14
SDA/PICO23: J93.3, J94.3, J96.3, R139.1, U24.14

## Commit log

2023-04-26 Add datasheet
2023-04-26 Add SparkX Eagle files
2023-04-26 Add BMI270 library file
    Also replace part in sch/brd files with new library part
2023-04-26 v10 updates
    Bump version number to v10
    Rename sch/brd files
    Move files into "1x1" folder in preparation for adding Qwiic Micro design
    Schematic:
    Update schematic frame
    Add "revised by"
2023-04-26 Fix vector fonts in schematic
    Old schematic had residual things from years ago causing schematic auto checklist to give warning about vector font. Just copied into new schematic to fix
    Also smashed power symbols to make power symbols use vector font
2023-04-27 Checklist updates
    Change max VDD to VDD range
    Add ordering instructions
    Add axis labels to bottom silk
    Add silk label to power LED
2023-04-27 Add Qwiic Micro version
2023-05-01 Design review updates
    Qwiic 1x1:
    Add y position of headers to measures
    Nudge I2C vias under right Qwiic connector
    Nudge vias away from silk
    Qwiic Micro:
    Remove traces and vias under chip
2023-05-01 Add "default" to I2C address in schematics
2023-05-01 Design review updates
    Add gap to linear axis silk to clarify gyro directions
    Add GND via to Qwiic Micro
2023-05-01 Silk tweaks
    Add silk lines between passive components
    Nudge "BMI270" silk on Qwiic Micro
    Add bigger pin 1 indicator dot to Qwiic Micro
2023-05-01 Add production files
2023-05-01 Remove PROD_ID from headers of 1x1
2023-06-08 Initial checkin of GitHub Pages
2023-06-08 Checkin updates
2023-06-09 Update photos of products
2023-06-09 Update Hookup Guide and Library links
2023-06-13 Updating Examples and links
2023-06-13 Updating contribute page links and required materials
2023-06-15 Correcting copy paste error
2023-06-20 Final hookup guide pics
    Final hookup guide pics
2023-06-21 Update main.html
    Changing single page link
2023-06-22 Testing framework changes
2024-02-23 Update to introduction formatting
2024-02-23 Deployed c8bb01b with MkDocs version: 1.5.3
